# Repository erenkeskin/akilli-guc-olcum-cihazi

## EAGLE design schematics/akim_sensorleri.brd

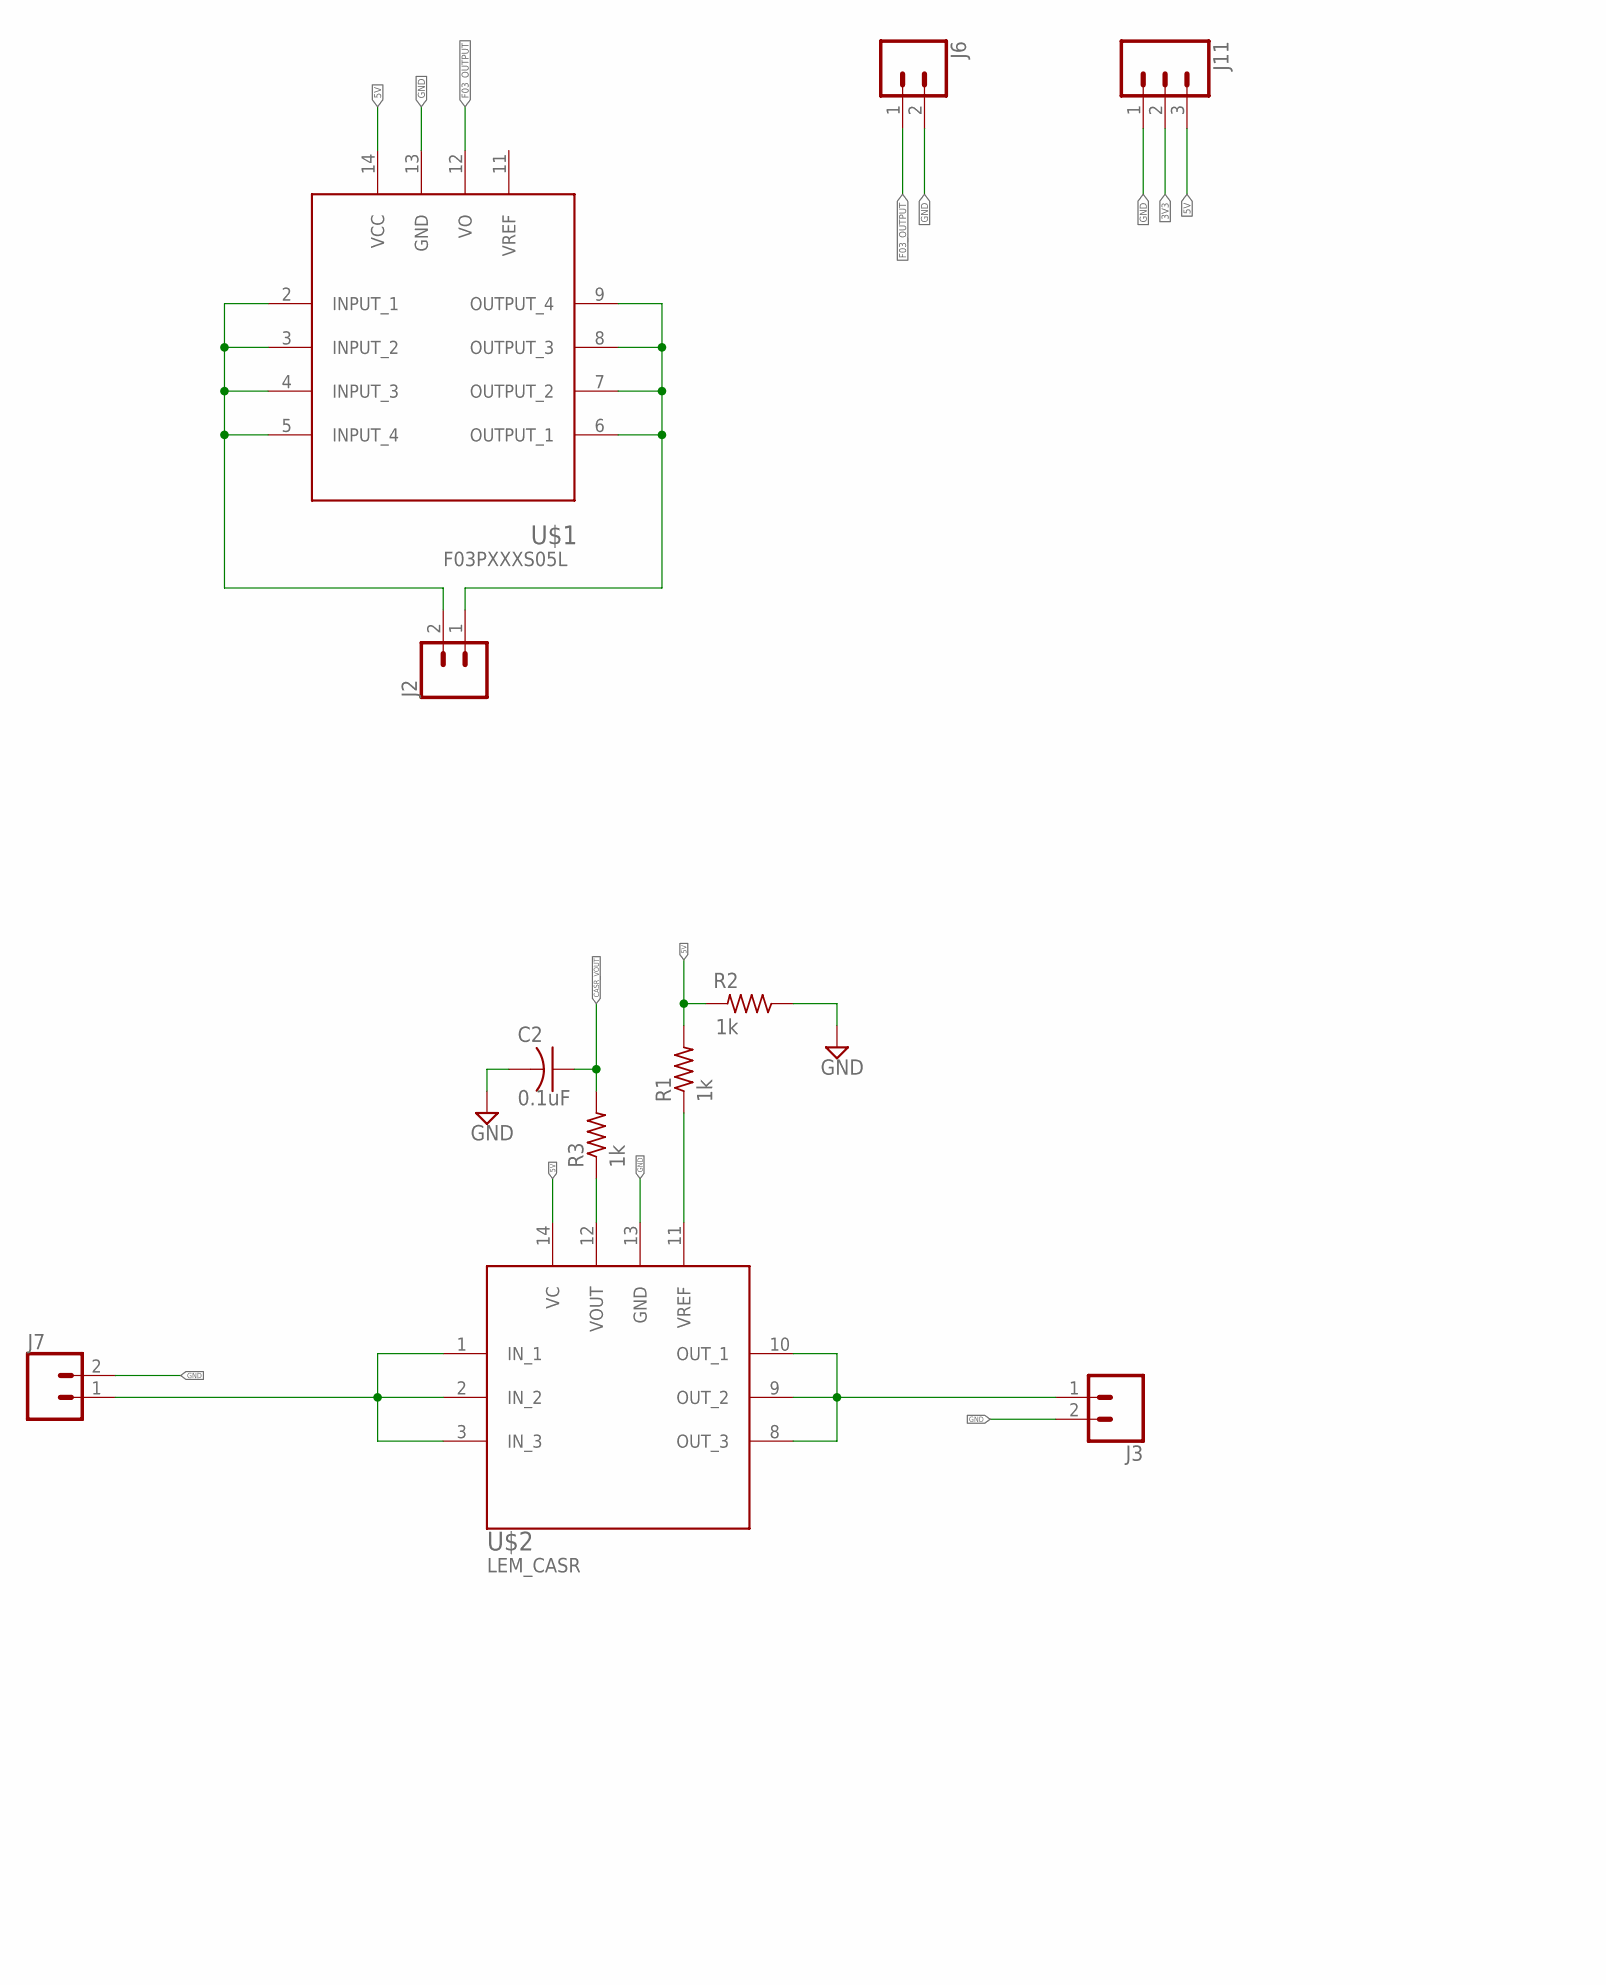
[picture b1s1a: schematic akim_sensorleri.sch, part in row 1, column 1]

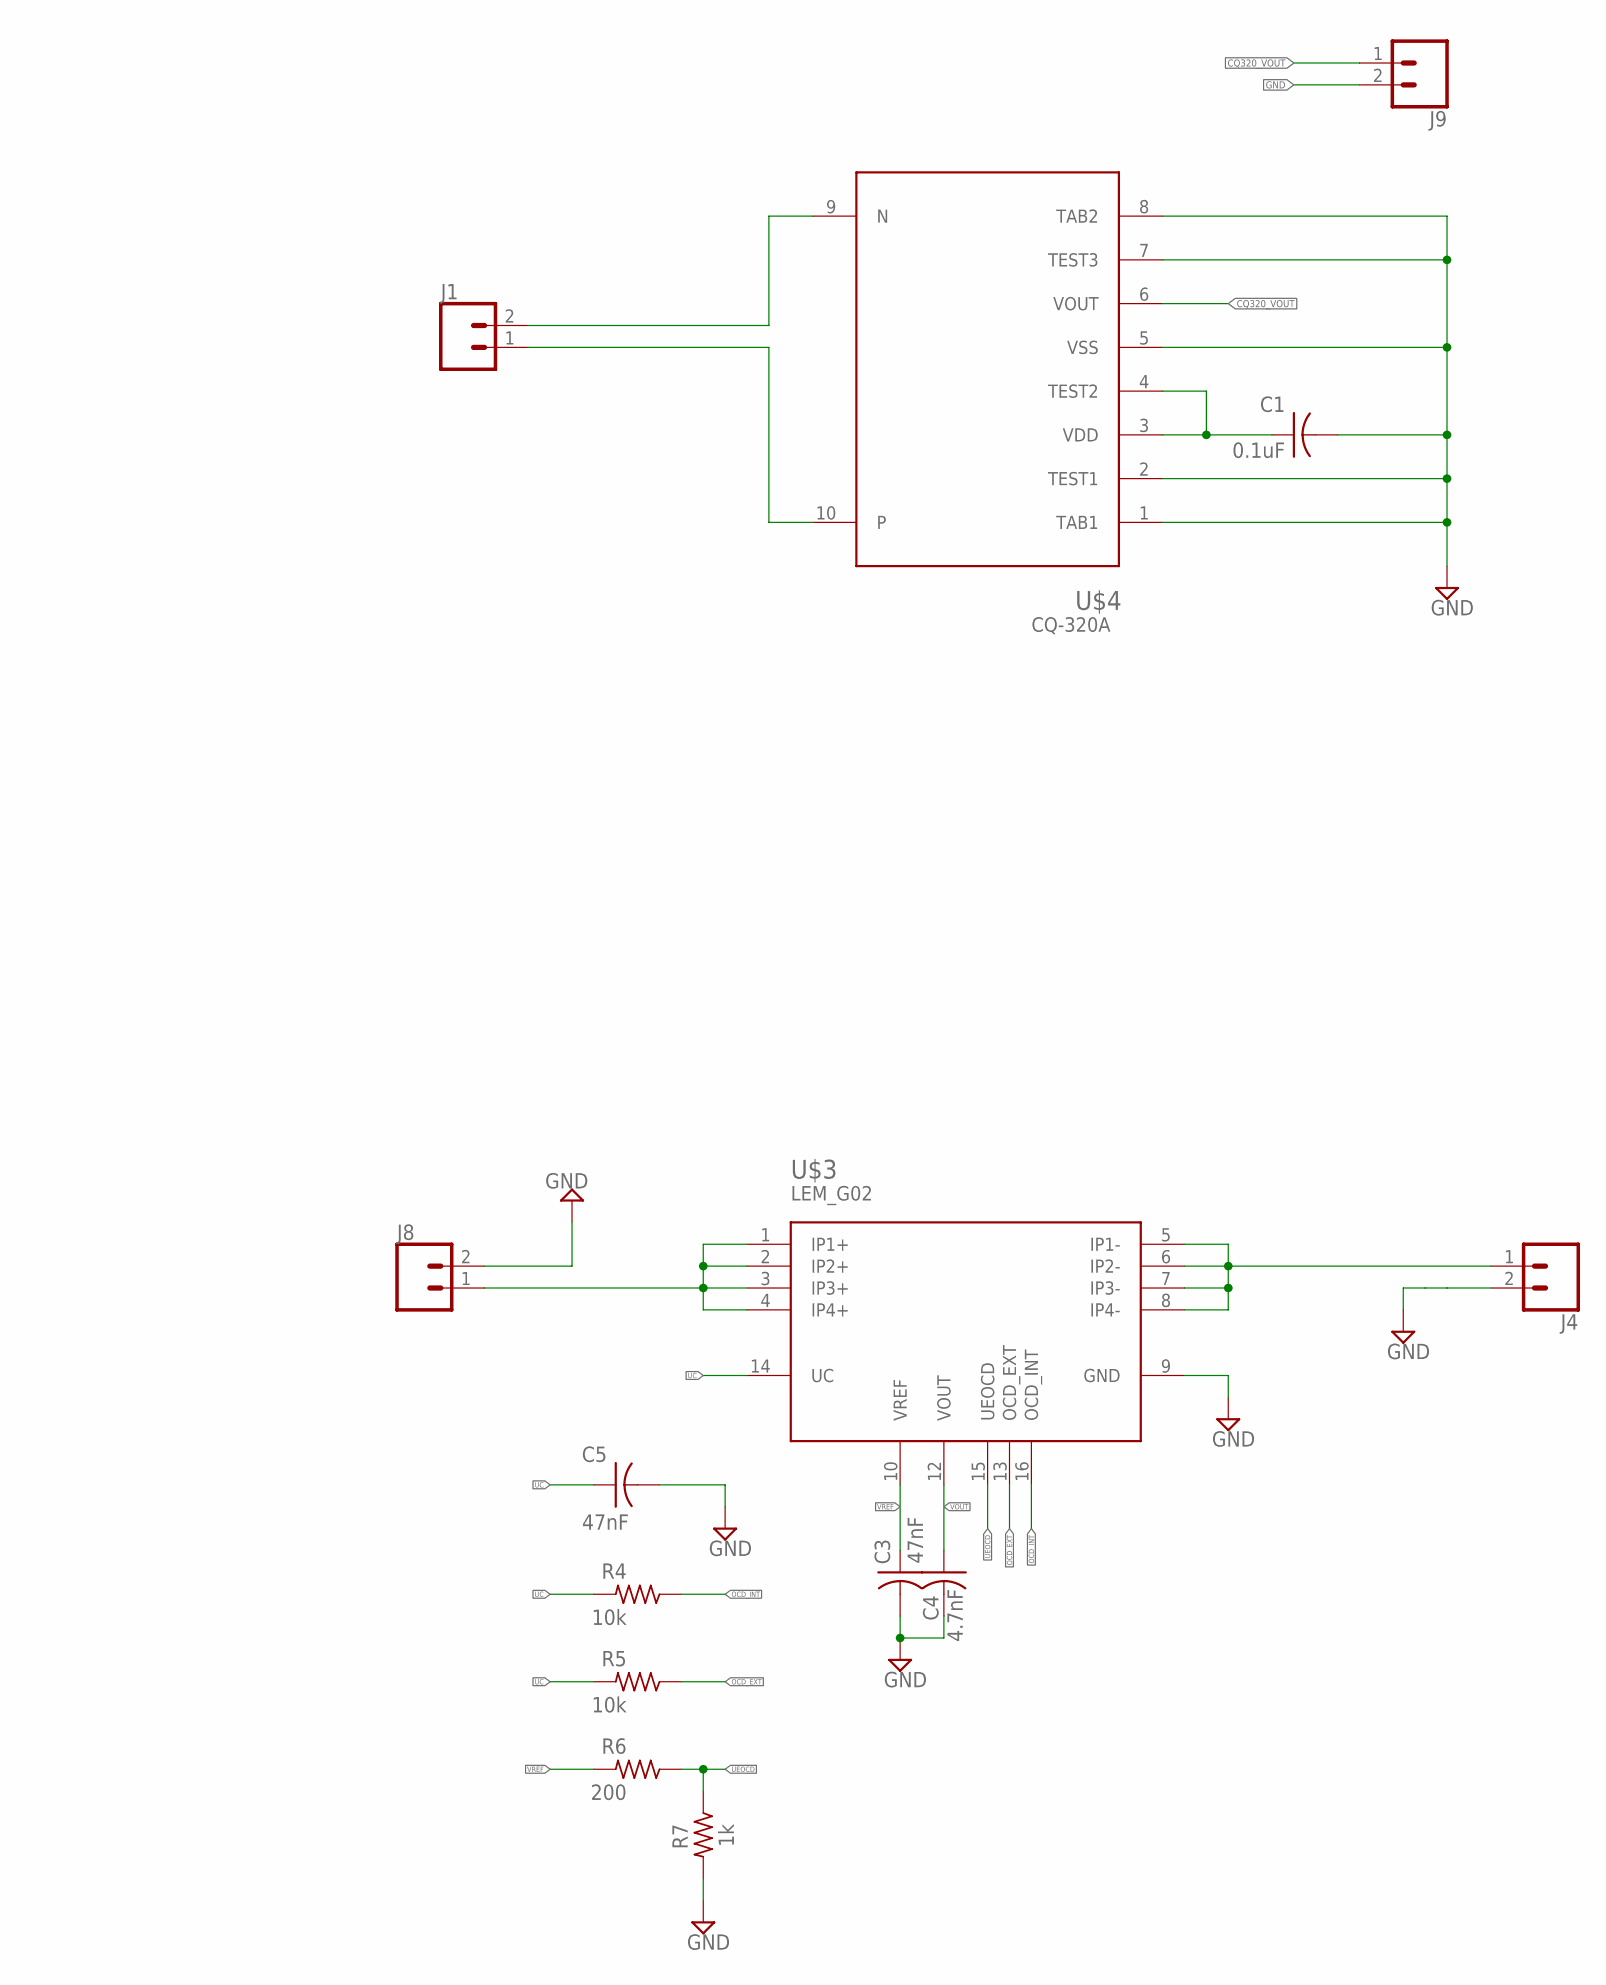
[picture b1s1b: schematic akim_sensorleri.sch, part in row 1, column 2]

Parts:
C1, C2: 0.1uF; C1206
C3, C5: 47nF; C1206
C4: 4.7nF; C1206
J1, J2, J3, J4, J6, J7, J8, J9: CONN_025MM; SCREWTERMINAL-5MM-2
J11: CONN_03-SCREW-5MM; SCREWTERMINAL-5MM-3
R1, R2, R3, R7: 1k; M1206
R4, R5: 10k; M1206
R6: 200; M1206
U$1: F03PXXXS05L
U$2: LEM_CASR; LEM
U$3: LEM_G02
U$4: CQ-320A

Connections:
3V3: J11.2
5V: J11.3, R1.2, R2.2, U$1.14 (VCC), U$2.14 (VC)
CASR_VOUT: C2.1, R3.2
CQ320_VOUT: J9.1, U$4.6 (VOUT)
F03_OUTPUT: J6.1, U$1.12 (VO)
GND: C1.2, C2.2, C3.2, C4.2, C5.2, J3.2, J4.2, J6.2, J7.2, J8.2, J9.2, J11.1, R2.1, R7.2, U$1.13 (GND), U$2.13 (GND), U$3.9 (GND), U$4.1 (TAB1), U$4.2 (TEST1), U$4.5 (VSS), U$4.7 (TEST3), U$4.8 (TAB2)
unnamed: J1.2, U$4.9 (N)
unnamed: J1.1, U$4.10
unnamed: R3.1, U$2.12 (VOUT)
unnamed: J4.1, U$3.5 (IP1-), U$3.6 (IP2-), U$3.7 (IP3-), U$3.8 (IP4-)
unnamed: R1.1, U$2.11 (VREF)
unnamed: J7.1, U$2.1 (IN_1), U$2.2 (IN_2), U$2.3 (IN_3)
unnamed: J8.1, U$3.1 (IP1+), U$3.2 (IP2+), U$3.3 (IP3+), U$3.4 (IP4+)
unnamed: J3.1, U$2.8 (OUT_3), U$2.9 (OUT_2), U$2.10 (OUT_1)
unnamed: J2.2, U$1.2 (INPUT_1), U$1.3 (INPUT_2), U$1.4 (INPUT_3), U$1.5 (INPUT_4)
unnamed: J2.1, U$1.6 (OUTPUT_1), U$1.7 (OUTPUT_2), U$1.8 (OUTPUT_3), U$1.9 (OUTPUT_4)
unnamed: C1.1, U$4.3 (VDD), U$4.4 (TEST2)
OCD_EXT: R5.1, U$3.13 (OCD_EXT)
OCD_INT: R4.1, U$3.16 (OCD_INT)
UC: C5.1, R4.2, R5.2, U$3.14 (UC)
UEOCD: R6.1, R7.1, U$3.15 (UEOCD)
VOUT: C4.1, U$3.12 (VOUT)
VREF: C3.1, R6.2, U$3.10 (VREF)

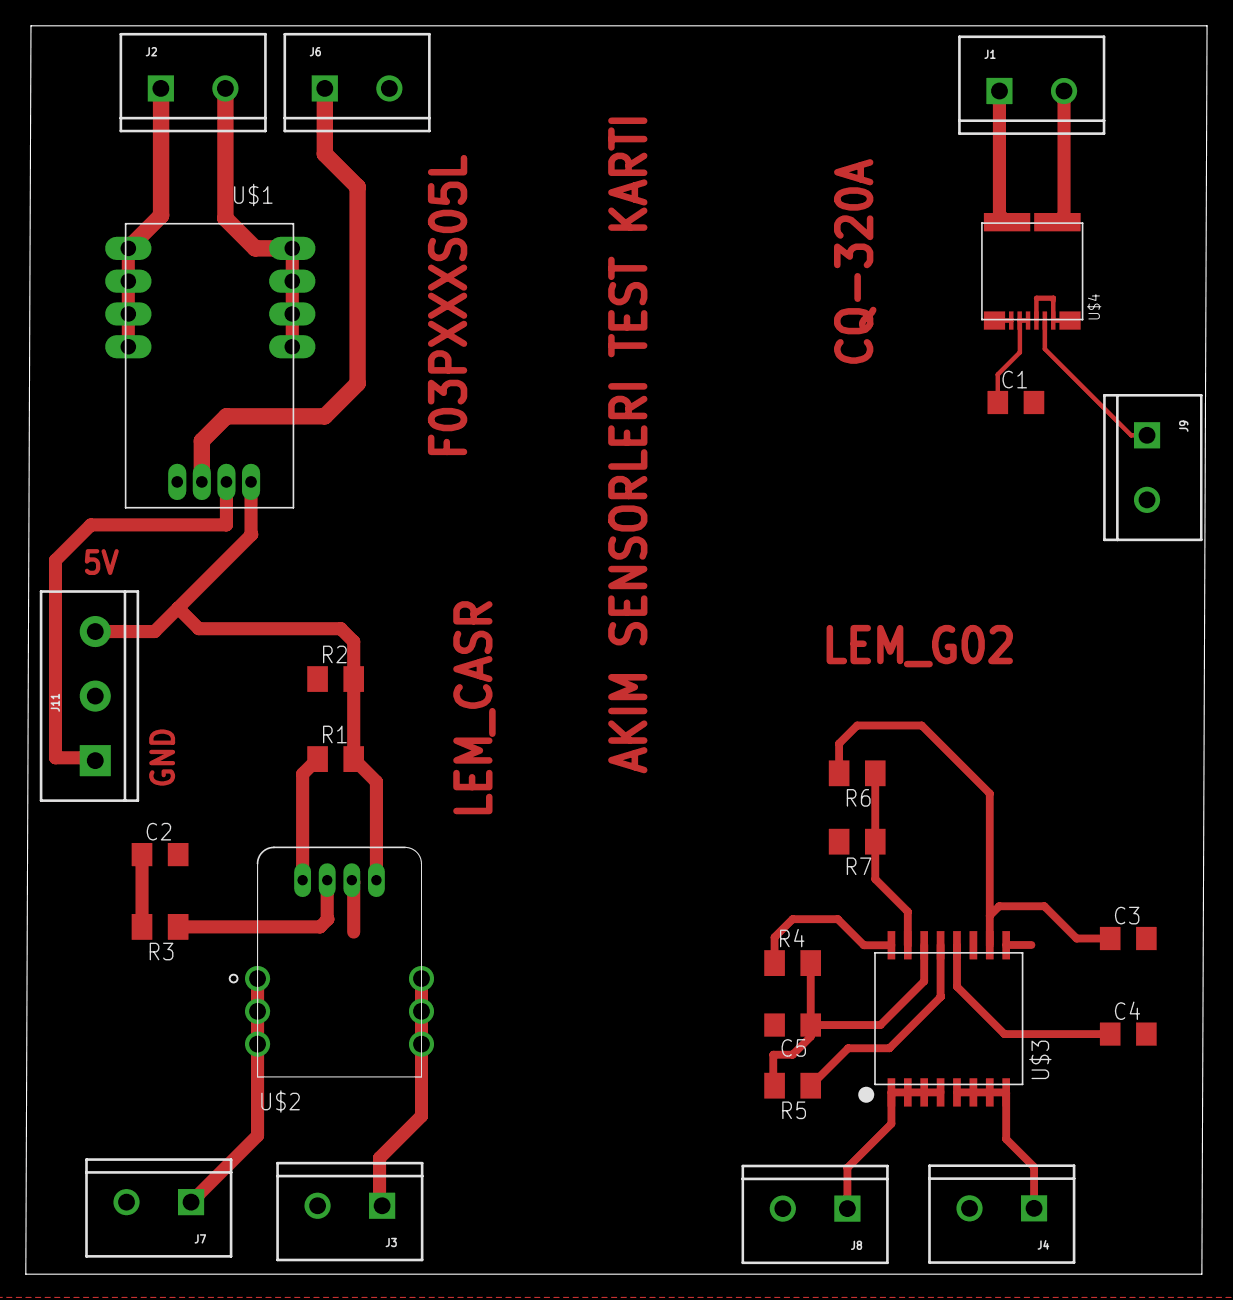
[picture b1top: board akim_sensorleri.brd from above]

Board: 2 copper layers, 91.5 x 96.7 mm, 25 parts (0 on the bottom side), 22 nets.

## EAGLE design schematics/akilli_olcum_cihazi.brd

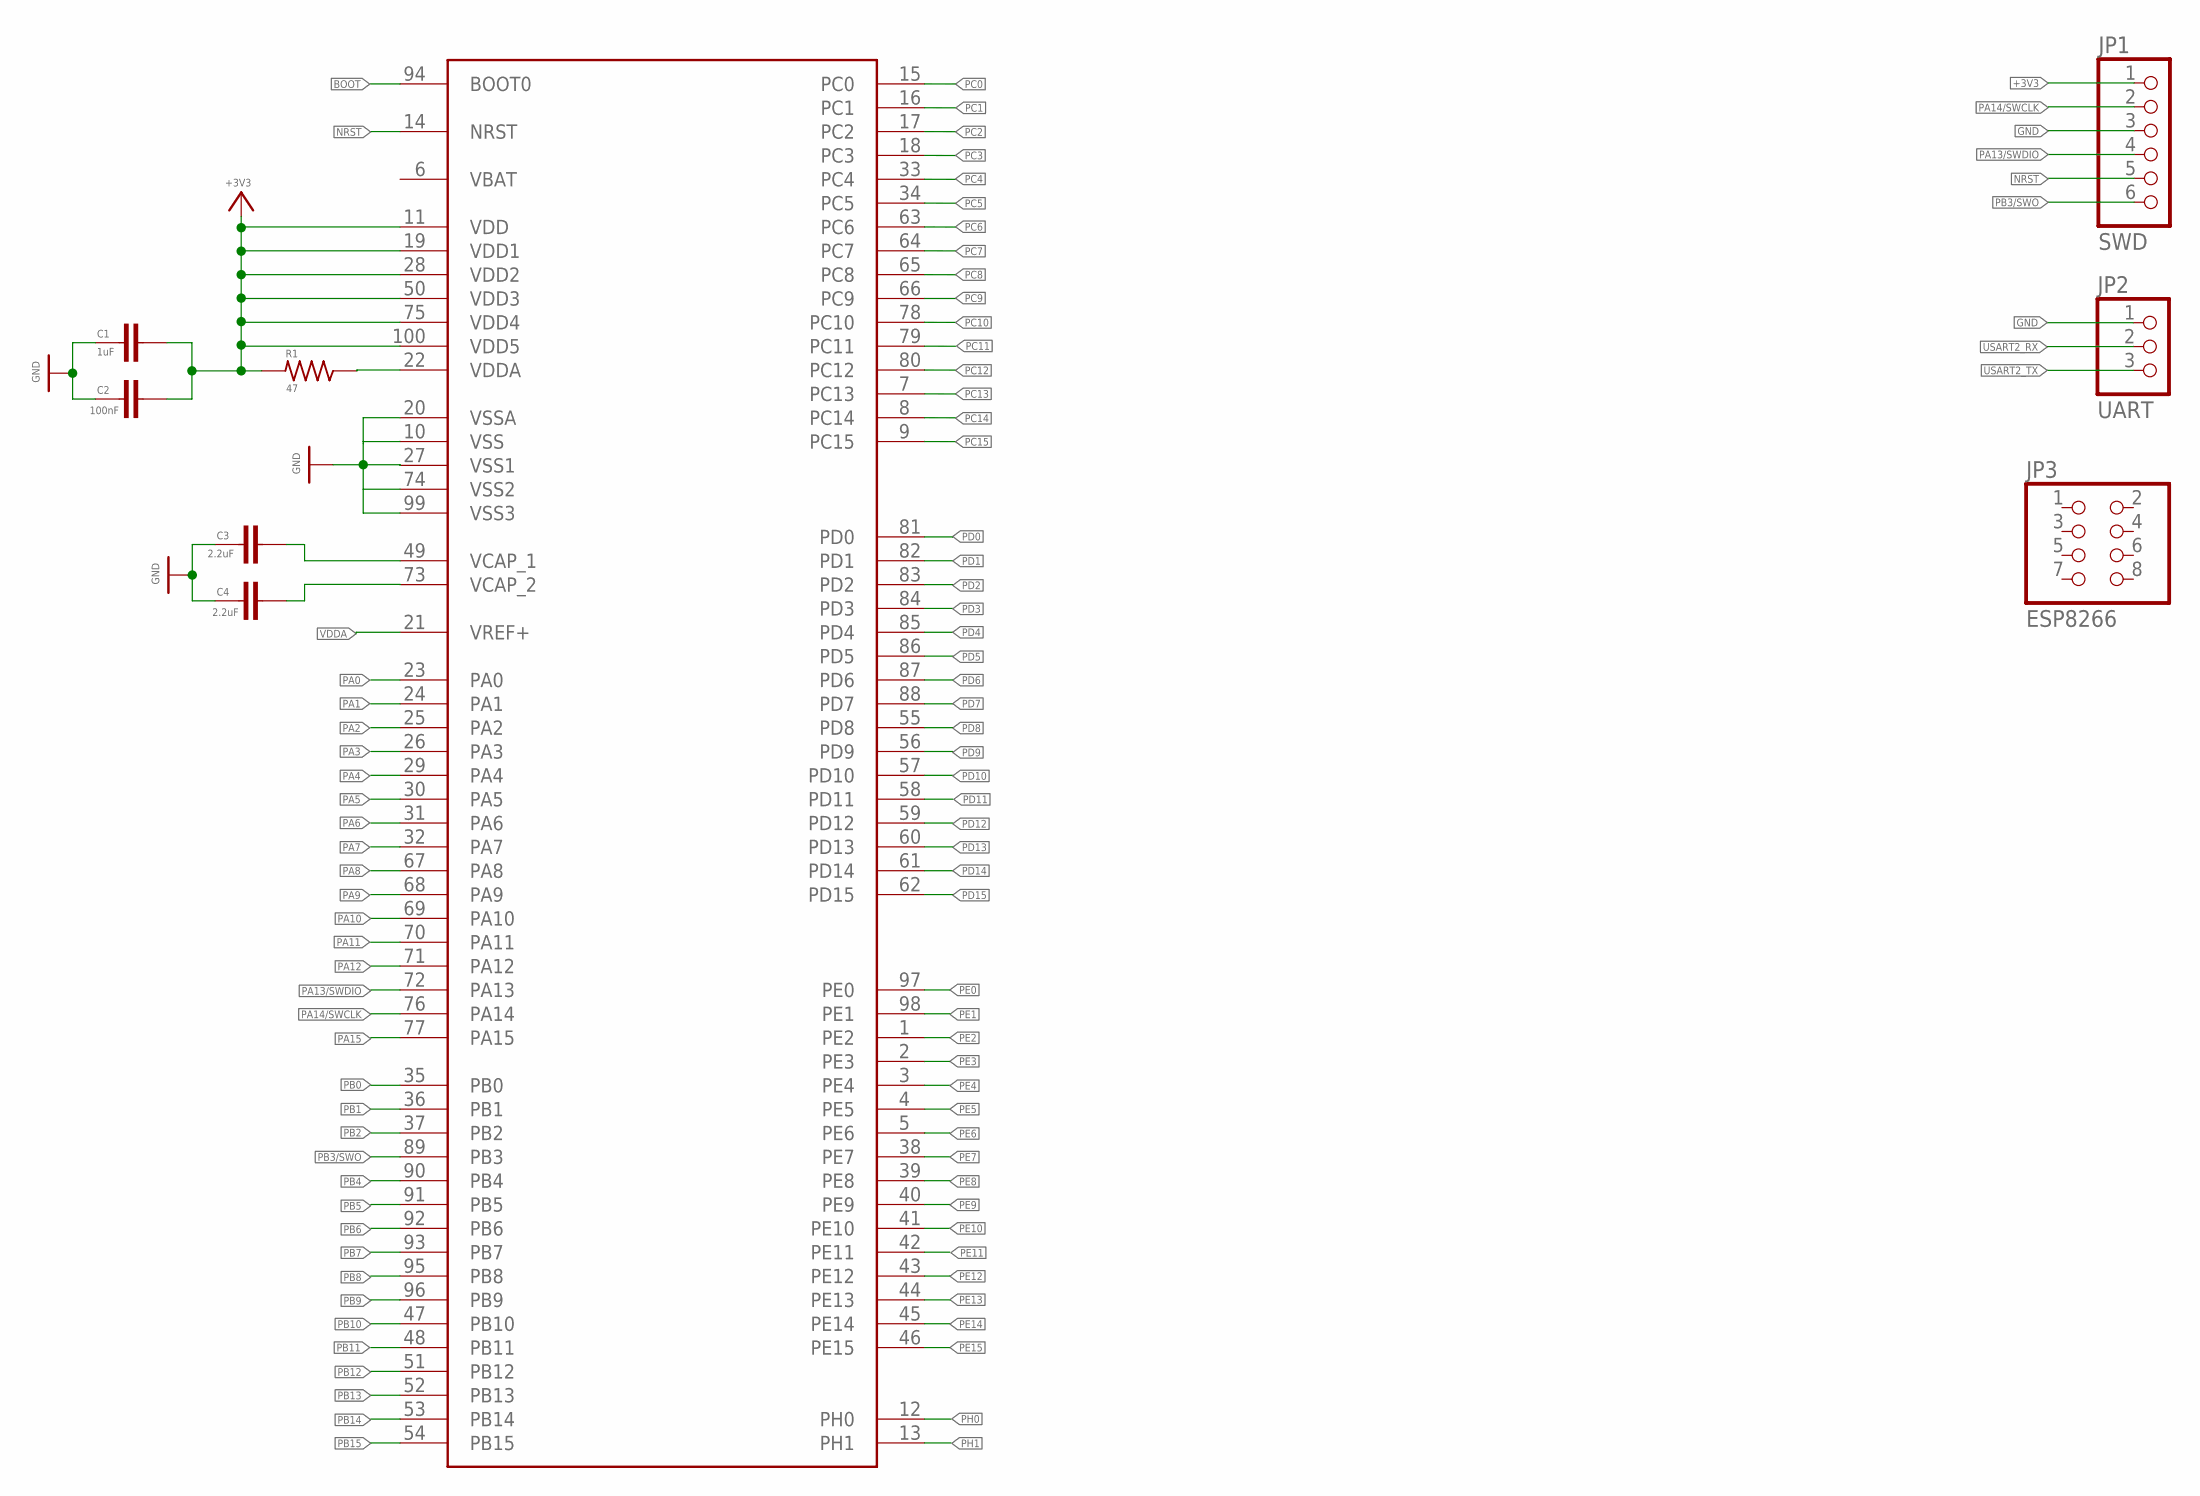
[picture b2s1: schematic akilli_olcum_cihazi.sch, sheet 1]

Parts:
C1: 1uF; C0805
C2: 100nF; C0805
C3, C4: 2.2uF; C0805
JP1: SWD; 1X06
JP2: UART; 1X03
JP3: ESP8266; 2X04
R1: 47; R1206
U$1: STM32F40XSTM32D40X; LQFP100

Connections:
+3V3: C1.2, C2.2, JP1.1, R1.2, U$1.11 (VDD), U$1.19 (VDD1), U$1.28 (VDD2), U$1.50 (VDD3), U$1.75 (VDD4), U$1.100 (VDD5)
BOOT: U$1.94 (BOOT0)
GND: C1.1, C2.1, C3.1, C4.1, JP1.3, JP2.1, U$1.10 (VSS), U$1.20 (VSSA), U$1.27 (VSS1), U$1.74 (VSS2), U$1.99 (VSS3)
unnamed: C3.2, U$1.49 (VCAP_1)
unnamed: C4.2, U$1.73 (VCAP_2)
NRST: JP1.5, U$1.14 (NRST)
PA0: U$1.23 (PA0)
PA1: U$1.24 (PA1)
PA2: U$1.25 (PA2)
PA3: U$1.26 (PA3)
PA4: U$1.29 (PA4)
PA5: U$1.30 (PA5)
PA6: U$1.31 (PA6)
PA7: U$1.32 (PA7)
PA8: U$1.67 (PA8)
PA9: U$1.68 (PA9)
PA10: U$1.69 (PA10)
PA11: U$1.70 (PA11)
PA12: U$1.71 (PA12)
PA13/SWDIO: JP1.4, U$1.72 (PA13)
PA14/SWCLK: JP1.2, U$1.76 (PA14)
PA15: U$1.77 (PA15)
PB0: U$1.35 (PB0)
PB1: U$1.36 (PB1)
PB2: U$1.37 (PB2)
PB3/SWO: JP1.6, U$1.89 (PB3)
PB4: U$1.90 (PB4)
PB5: U$1.91 (PB5)
PB6: U$1.92 (PB6)
PB7: U$1.93 (PB7)
PB8: U$1.95 (PB8)
PB9: U$1.96 (PB9)
PB10: U$1.47 (PB10)
PB11: U$1.48 (PB11)
PB12: U$1.51 (PB12)
PB13: U$1.52 (PB13)
PB14: U$1.53 (PB14)
PB15: U$1.54 (PB15)
PC0: U$1.15 (PC0)
PC1: U$1.16 (PC1)
PC2: U$1.17 (PC2)
PC3: U$1.18 (PC3)
PC4: U$1.33 (PC4)
PC5: U$1.34 (PC5)
PC6: U$1.63 (PC6)
PC7: U$1.64 (PC7)
PC8: U$1.65 (PC8)
PC9: U$1.66 (PC9)
PC10: U$1.78 (PC10)
PC11: U$1.79 (PC11)
PC12: U$1.80 (PC12)
PC13: U$1.7 (PC13)
PC14: U$1.8 (PC14)
PC15: U$1.9 (PC15)
PD0: U$1.81 (PD0)
PD1: U$1.82 (PD1)
PD2: U$1.83 (PD2)
PD3: U$1.84 (PD3)
PD4: U$1.85 (PD4)
PD5: U$1.86 (PD5)
PD6: U$1.87 (PD6)
PD7: U$1.88 (PD7)
PD8: U$1.55 (PD8)
PD9: U$1.56 (PD9)
PD10: U$1.57 (PD10)
PD11: U$1.58 (PD11)
PD12: U$1.59 (PD12)
PD13: U$1.60 (PD13)
PD14: U$1.61 (PD14)
PD15: U$1.62 (PD15)
PE0: U$1.97 (PE0)
PE1: U$1.98 (PE1)
PE2: U$1.1 (PE2)
PE3: U$1.2 (PE3)
PE4: U$1.3 (PE4)
PE5: U$1.4 (PE5)
PE6: U$1.5 (PE6)
PE7: U$1.38 (PE7)
PE8: U$1.39 (PE8)
PE9: U$1.40 (PE9)
PE10: U$1.41 (PE10)
PE11: U$1.42 (PE11)
PE12: U$1.43 (PE12)
PE13: U$1.44 (PE13)
PE14: U$1.45 (PE14)
PE15: U$1.46 (PE15)
PH0: U$1.12 (PH0)
PH1: U$1.13 (PH1)
USART2_RX: JP2.2
USART2_TX: JP2.3
VDDA: R1.1, U$1.21 (VREF+), U$1.22 (VDDA)

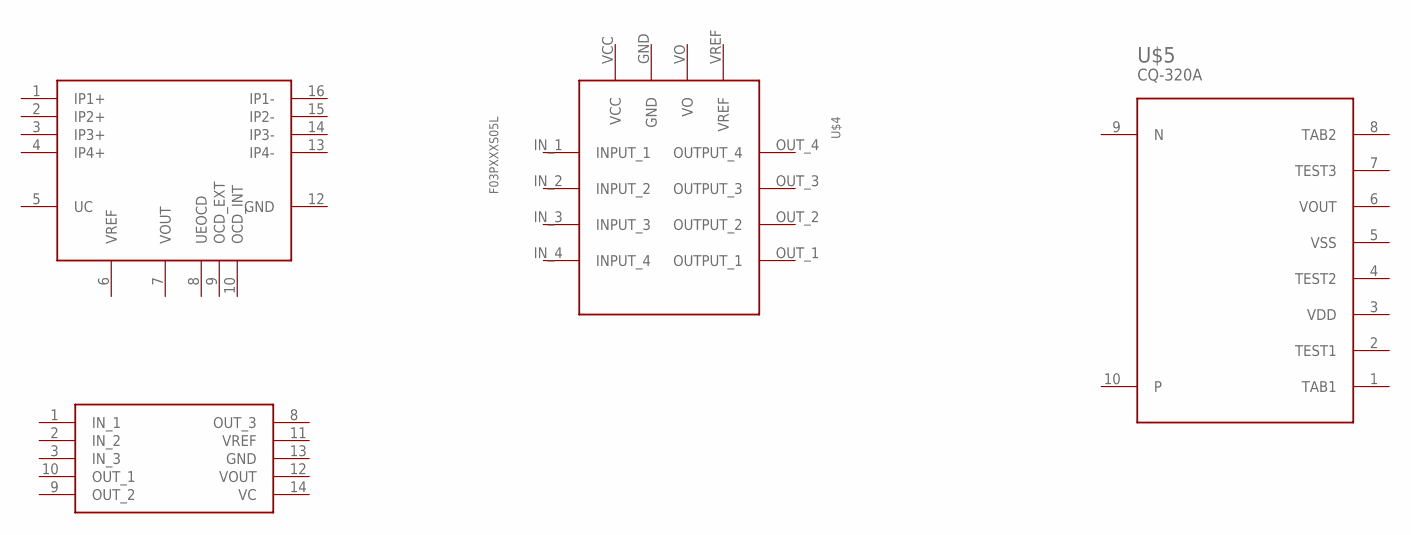
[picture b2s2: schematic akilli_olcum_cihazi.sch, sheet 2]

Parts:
U$2: LEM_G02
U$3: LEM_CASR; LEM
U$4: F03PXXXS05L
U$5: CQ-320A

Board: 2 copper layers, 13 parts (0 on the bottom side), 9 nets, no tracks yet.

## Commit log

2019-02-14 Sinyal verileri alindi
2019-02-14 Schematics Added

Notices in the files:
parts and their libraries:
SparkFun-Connectors: Licensing: Creative Commons ShareAlike 4.0 International - https://creativecommons.org/licenses/by-sa/4.0
